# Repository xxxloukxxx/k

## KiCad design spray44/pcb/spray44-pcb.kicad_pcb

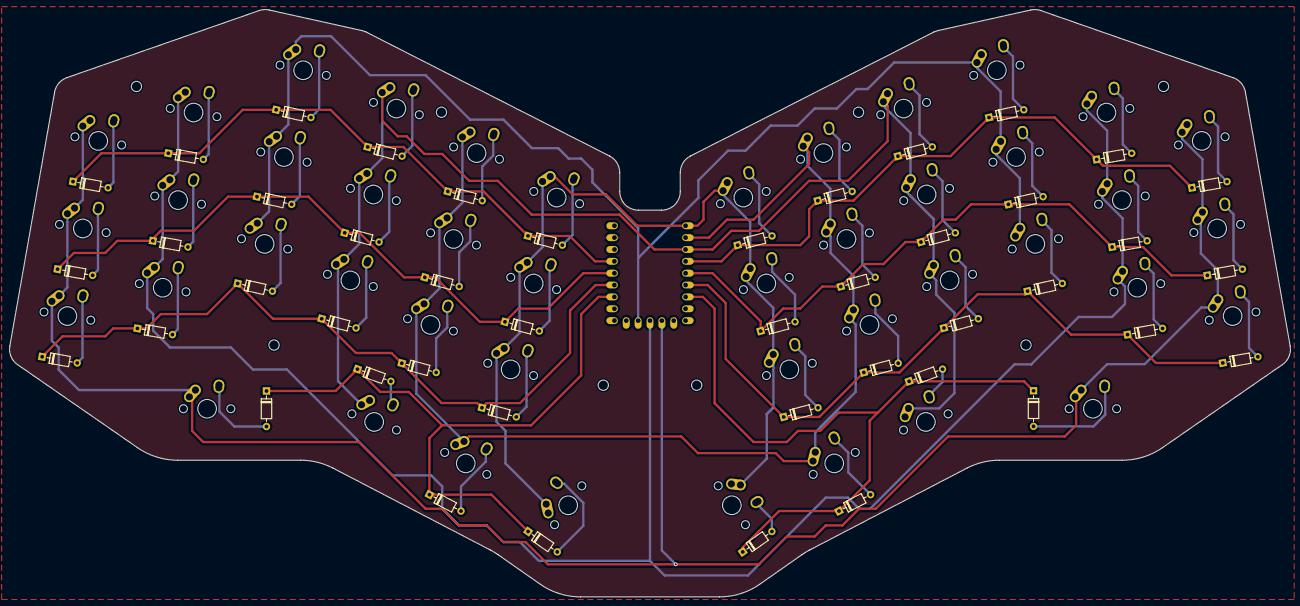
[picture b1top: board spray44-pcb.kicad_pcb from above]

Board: 2 copper layers, 274.4 x 125.8 mm, 97 parts (0 on the bottom side), 58 nets.

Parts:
D1, D2, D3, D4, D5, D6, D7, D8, D9, D10, D11, D12, D13, D14, D15, D16, D17, D18, D19, D20, D21, D22, D23, D24, D25, D26, D27, D28, D29, D30, D31, D32, D33, D34, D35, D36, D37, D38, D39, D40, D41, D42, D43, D44: 1N4148; D_DO-35_SOD27_P7.62mm_Horizontal
H1, H2, H3, H4, H5, H6, H7, H8: MountingHole; MountingHole_2.2mm_M2
MX1, MX2, MX3, MX4, MX5, MX6, MX7, MX8, MX9, MX10, MX11, MX12, MX13, MX14, MX15, MX16, MX17, MX18, MX19, MX20, MX21, MX22, MX23, MX24, MX25, MX26, MX27, MX28, MX29, MX30, MX31, MX32, MX33, MX34, MX35, MX36, MX38, MX39, MX42, MX43: MX; MX-Alps-Hybrid-1U
MX37, MX44: MX; MX-Alps-Hybrid-1.25U
MX40, MX41: MX; MX-Alps-Hybrid-1.5U
U1: rp2040-zero; rp2040-zero-tht

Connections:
C1: MX1.1 (COL), MX12.1 (COL), MX13.1 (COL), MX24.1 (COL), MX25.1 (COL), MX36.1 (COL), MX37.1 (COL), MX44.1 (COL), U1.11 (10)
C2: MX2.1 (COL), MX11.1 (COL), MX14.1 (COL), MX23.1 (COL), MX26.1 (COL), MX35.1 (COL), U1.12 (11)
C3: MX3.1 (COL), MX10.1 (COL), MX15.1 (COL), MX22.1 (COL), MX27.1 (COL), MX34.1 (COL), U1.13 (12)
C4: MX4.1 (COL), MX9.1 (COL), MX16.1 (COL), MX21.1 (COL), MX28.1 (COL), MX33.1 (COL), MX38.1 (COL), MX43.1 (COL), U1.3 (2)
C5: MX5.1 (COL), MX8.1 (COL), MX17.1 (COL), MX20.1 (COL), MX29.1 (COL), MX32.1 (COL), MX39.1 (COL), MX42.1 (COL), U1.2 (1)
C6: MX6.1 (COL), MX7.1 (COL), MX18.1 (COL), MX19.1 (COL), MX30.1 (COL), MX31.1 (COL), MX40.1 (COL), MX41.1 (COL), U1.1 (0)
L1: D1.1 (K), D2.1 (K), D3.1 (K), D4.1 (K), D5.1 (K), D6.1 (K), U1.20 (29)
L2: D13.1 (K), D14.1 (K), D15.1 (K), D16.1 (K), D17.1 (K), D18.1 (K), U1.19 (28)
L3: D25.1 (K), D26.1 (K), D27.1 (K), D28.1 (K), D29.1 (K), D30.1 (K), U1.18 (27)
L4: D37.1 (K), D38.1 (K), D39.1 (K), D40.1 (K), U1.17 (26)
L5: D7.1 (K), D8.1 (K), D9.1 (K), D10.1 (K), D11.1 (K), D12.1 (K), U1.4 (3)
L6: D19.1 (K), D20.1 (K), D21.1 (K), D22.1 (K), D23.1 (K), D24.1 (K), U1.5 (4)
L7: D31.1 (K), D32.1 (K), D33.1 (K), D34.1 (K), D35.1 (K), D36.1 (K), U1.6 (5)
L8: D41.1 (K), D42.1 (K), D43.1 (K), D44.1 (K), U1.7 (6)
unnamed: D1.2 (A), MX1.2 (ROW)
unnamed: D2.2 (A), MX2.2 (ROW)
unnamed: D3.2 (A), MX3.2 (ROW)
unnamed: D4.2 (A), MX4.2 (ROW)
unnamed: D5.2 (A), MX5.2 (ROW)
unnamed: D6.2 (A), MX6.2 (ROW)
unnamed: D7.2 (A), MX7.2 (ROW)
unnamed: D8.2 (A), MX8.2 (ROW)
unnamed: D9.2 (A), MX9.2 (ROW)
unnamed: D10.2 (A), MX10.2 (ROW)
unnamed: D11.2 (A), MX11.2 (ROW)
unnamed: D12.2 (A), MX12.2 (ROW)
unnamed: D13.2 (A), MX13.2 (ROW)
unnamed: D14.2 (A), MX14.2 (ROW)
unnamed: D15.2 (A), MX15.2 (ROW)
unnamed: D16.2 (A), MX16.2 (ROW)
unnamed: D17.2 (A), MX17.2 (ROW)
unnamed: D18.2 (A), MX18.2 (ROW)
unnamed: D19.2 (A), MX19.2 (ROW)
unnamed: D20.2 (A), MX20.2 (ROW)
unnamed: D21.2 (A), MX21.2 (ROW)
unnamed: D22.2 (A), MX22.2 (ROW)
unnamed: D23.2 (A), MX23.2 (ROW)
unnamed: D24.2 (A), MX24.2 (ROW)
unnamed: D25.2 (A), MX25.2 (ROW)
unnamed: D26.2 (A), MX26.2 (ROW)
unnamed: D27.2 (A), MX27.2 (ROW)
unnamed: D28.2 (A), MX28.2 (ROW)
unnamed: D29.2 (A), MX29.2 (ROW)
unnamed: D30.2 (A), MX30.2 (ROW)
unnamed: D31.2 (A), MX31.2 (ROW)
unnamed: D32.2 (A), MX32.2 (ROW)
unnamed: D33.2 (A), MX33.2 (ROW)
unnamed: D34.2 (A), MX34.2 (ROW)
unnamed: D35.2 (A), MX35.2 (ROW)
unnamed: D36.2 (A), MX36.2 (ROW)
unnamed: D37.2 (A), MX37.2 (ROW)
unnamed: D38.2 (A), MX38.2 (ROW)
unnamed: D39.2 (A), MX39.2 (ROW)
unnamed: D40.2 (A), MX40.2 (ROW)
unnamed: D41.2 (A), MX41.2 (ROW)
unnamed: D42.2 (A), MX42.2 (ROW)
unnamed: D43.2 (A), MX43.2 (ROW)
unnamed: D44.2 (A), MX44.2 (ROW)
